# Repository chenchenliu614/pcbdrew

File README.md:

# PcbDraw

Transform your KiCAD PCB into a beautiful 2D diagram for pinout diagrams or other documentation purposes. No more tedious manual schematic drawings or assembling screenshots!

This tool reads a `.kicad_pcb` file and generates an elegant, SVG-formatted 2D PCB image. Simply insert the generated image into your documentation or README, and you don’t need to have a physical board or open KiCAD to capture a screenshot. Both you and your readers will enjoy a clear, intuitive view of your board layout!

PcbDraw also includes a companion tool—**Populate**—designed to help you easily create and maintain neat assembly manuals in HTML or Markdown format, for instance, by quickly indicating which components to solder where and how to assemble the board.

## Installation

Besides generating 2D diagrams, PcbDraw enables you to programmatically obtain a 3D rendering preview of your PCB (for example, within CI workflows), making it easier to automate the generation of hardware documentation or test reports.

The tool is distributed as a Python package named `pcbdraw` that includes a standalone command-line utility. Note that some library functions require the local installation of [Inkscape](https://inkscape.org/).

### 1. System Dependencies

- [Python 3](https://www.python.org/)
- [Inkscape](https://inkscape.org/)
- It is recommended that you use a virtual environment (virtualenv or conda) to manage dependencies and avoid conflicts.

### 2. Installation Steps

1. **Install PcbDraw**

   ```bash
   pip install pcbdraw
   ```

   If you need additional functionality for handling SVG paths or similar tasks, you may also install other common dependencies:

   ```bash
   pip install svgpathtools
   ```

2. **Verify the Installation**

   ```bash
   pcbdraw --version
   ```
   If a version number or help information is displayed, the installation was successful.

3. **(Optional) Install Populate**

   The Populate tool is typically provided with PcbDraw, but it can also be used on its own. If you need to create HTML/Markdown assembly manuals, consult the Populate documentation and examples for further details.

## Usage

You can find usage examples and scripts in the project's examples directory or the official documentation. The following is a brief demonstration of the basic functionality:

1. **Converting a KiCAD PCB File**

   ```bash
   pcbdraw my_board.kicad_pcb my_board.svg
   ```
   After a brief wait, a 2D PCB diagram named `my_board.svg` will be generated in your current directory.

2. **Generating a 3D Preview** (Optional – additional configuration required)  
   If you require a 3D preview in your CI or automated scripts, please refer to the official documentation for additional setup steps and include the appropriate parameters in your command.

3. **Using the Populate Tool**  
   Populate can generate a concise assembly manual page based on your BOM or other files. For example:
   ```bash
   populate generate my_board.bom.csv --template=html > my_manual.html
   ```
   This command will output a basic assembly manual for your review or sharing.

For further usage details and configuration options, please refer to the [examples](./examples) directory or check the output of `pcbdraw --help` and `populate --help`.

## "PcbDraw Seems Broken"

If you run into any issues during usage or if the functionality does not meet your requirements, please feel free to open an issue on the [Issues](./issues) page. We highly appreciate community feedback and will do our best to help troubleshoot and resolve any problems.

## Contributing

- If you wish to submit new features or bug fixes, feel free to fork the repository and create a pull request.
- For feature requests or suggestions for improvements, please leave a comment in [Issues](./issues).

## Future Work

- We plan to gradually refine and add more modules to support a wider range of PCB layouts and components.
- In the future, we may further optimize automated 3D preview generation and integrate it with additional CI services.

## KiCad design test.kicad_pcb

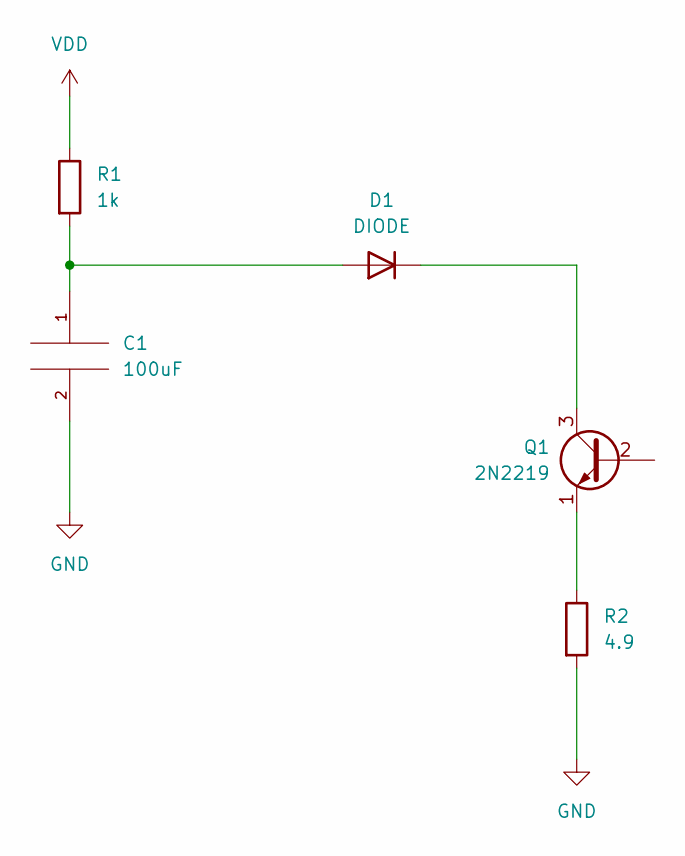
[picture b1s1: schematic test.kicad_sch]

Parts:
C1: 100uF; CP_EIA-1608-08_AVX-J
D1: DIODE; D_0201_0603Metric
Q1: 2N2219; TO-39-3
R1: 1k; R_0402_1005Metric
R2: 4.9; R_0402_1005Metric

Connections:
GND: C1.2, R2.2
unnamed: D1.2 (K), Q1.3 (C)
unnamed: C1.1, D1.1 (A), R1.2
unnamed: Q1.1 (E), R2.1
VDD: R1.1

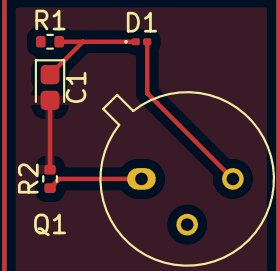
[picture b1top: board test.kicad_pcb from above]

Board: 2 copper layers, 5 parts (0 on the bottom side), 4 nets.

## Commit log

2025-03-28 Create Update installation instructions on MacOS
2025-03-28 Update Update installation instructions on MacOS
2025-04-08 Create ModuleNotFoundError: No module named 'pcbnew'
    issue
2025-04-08 Update ModuleNotFoundError: No module named 'pcbnew'
2025-04-08 Create solution
2025-04-15 Create Example
2025-04-15 Example
    This is a PCB layout I drew myself; using it as an example, you can obtain beautiful 2D diagrams.
